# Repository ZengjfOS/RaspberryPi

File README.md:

# README

个人认为，树莓派应该算是目前开源硬件里学习嵌入式Linux系统最好的工具，里面的设计思路和一些工具是很值得借鉴的，这里主要使用Raspberry Pi 4B进行系统架构分析。

## 40 Pin引脚

## Refers

## docs

NO.|文件名称|摘要
:--:|:--|:--
0027| [制作风扇扩展板FanHAT](docs/0027_制作风扇扩展板FanHAT.md) | KiCad制作风扇扩展板FanHaT
0026| [git服务器](docs/0026_git服务器.md) | 搭建git服务器
0025| [硬件PWM控制风扇](docs/0025_硬件PWM控制风扇.md) | PWM控制风扇
0024| [采用V4L2接口获取USB摄像头图片](docs/0024_采用V4L2接口获取USB摄像头图片.md) | C语言获取图片可以更好理解V4L2接口
0023| [关于如何学习](docs/0023_关于如何学习.md) | 记录是最好的反思
0022| [SD卡自动扩容](docs/0022_SD卡自动扩容.md) | 理解SD卡自动扩容工作原理
0021| [wav声音PCM数据分析](docs/0021_wav声音PCM数据分析.md) | 通过wav文件了解PCM数据
0020| [Android_Binder通信](docs/0020_Android_Binder通信.md) | 在树莓派中理解Android Binder通信
0019| [USB_OTG虚拟串口](docs/0019_USB_OTG虚拟串口.md) | USB OTG虚拟串口，可用于学习串口通信
0018| [利用AT24C02_EEPROM理解I2C通信](docs/0018_利用AT24C02_EEPROM理解I2C通信.md) | 利用Overlay加载AT24C02 I2C驱动，通过i2c-tools获取数据
0017| [GPIO中断模式控制网页](docs/0017_GPIO中断模式控制网页.md) | 通过Python3 Flask/websocket作为服务端，使用GPIO控制网页背景
0016| [IoT网页GPIO控制LED](docs/0016_IoT网页GPIO控制LED.md) | 通过Python3 Flask作为HTTP服务端，控制GPIO
0015| [用户空间控制GPIO](docs/0015_用户空间控制GPIO.md) | 通过使用内核GPIO Sysfs Interface在用户空间控制LED
0014| [动态设备树GPIO控制LED](docs/0014_动态设备树GPIO控制LED.md) | 通过使用动态改变设备树，使用内核gpio-poweroff驱动实现LED控制
0013| [开机自动发IP信息邮件](docs/0013_开机自动发IP信息邮件.md) | Python3自动发邮件
0012| [dtparam_dtoverlay_DTS动态设备树](docs/0012_dtparam_dtoverlay_DTS动态设备树.md) | 分析dtparam/dtoverlay本质，为什么能够动态改变设备与驱动的match
0011| [SoC设备树DTS分析](docs/0011_SoC设备树DTS分析.md) | 怎么分析芯片设备树
0010| [Tmux_Vim_Ctags_Cscope代码分析](docs/0010_Tmux_Vim_Ctags_Cscope代码分析.md) | 在Linux命令行如何阅读代码？
0009| [USB摄像头搭建IP网络摄像头](docs/0009_USB摄像头搭建IP网络摄像头.md) | 使用USB Camera搭建IP Camera，理解IP Camera工作原理
0008| [USB摄像头分析udev加载驱动原理](docs/0008_USB摄像头分析udev加载驱动原理.md) | 使用USB Camera分析udev加载驱动原理，理解udev工作原理
0007| [Systemd进程启动](docs/0007_Systemd进程启动.md) | 分析Linux系统进程何启动起来
0006| [搭建samba服务端](docs/0006_搭建samba服务端.md) | 像访问普通文件夹一样访问树莓派文件系统
0005| [内核编译](docs/0005_内核编译.md) | 编译Linux内核，以备后续修改及分析驱动
0004| [Debug串口](docs/0004_Debug串口.md) | 看内核启动log信息，当机器无法启动可以判定问题
0003| [开源软件镜像站加速](docs/0003_开源软件镜像站加速.md) | 时间很宝贵，只介绍apt、pip镜像站，其他可自行扩展
0002| [USB_OTG虚拟网卡](docs/0002_USB_OTG虚拟网卡.md) | 在有些场合，没有Wifi想登陆树莓派，使用USB虚拟网卡SSH登陆
0001| [无屏如何使用树莓派](docs/0001_无屏如何使用树莓派.md) | 一个屏比一个树莓派还贵，不大可能为了玩个树莓派还单独买个屏，并不是每个人都有屏的需求

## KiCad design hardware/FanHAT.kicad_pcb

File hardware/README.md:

# README

风扇HAT板KiCad工程

## 打样

* [FanHAT.zip](FanHAT.zip)

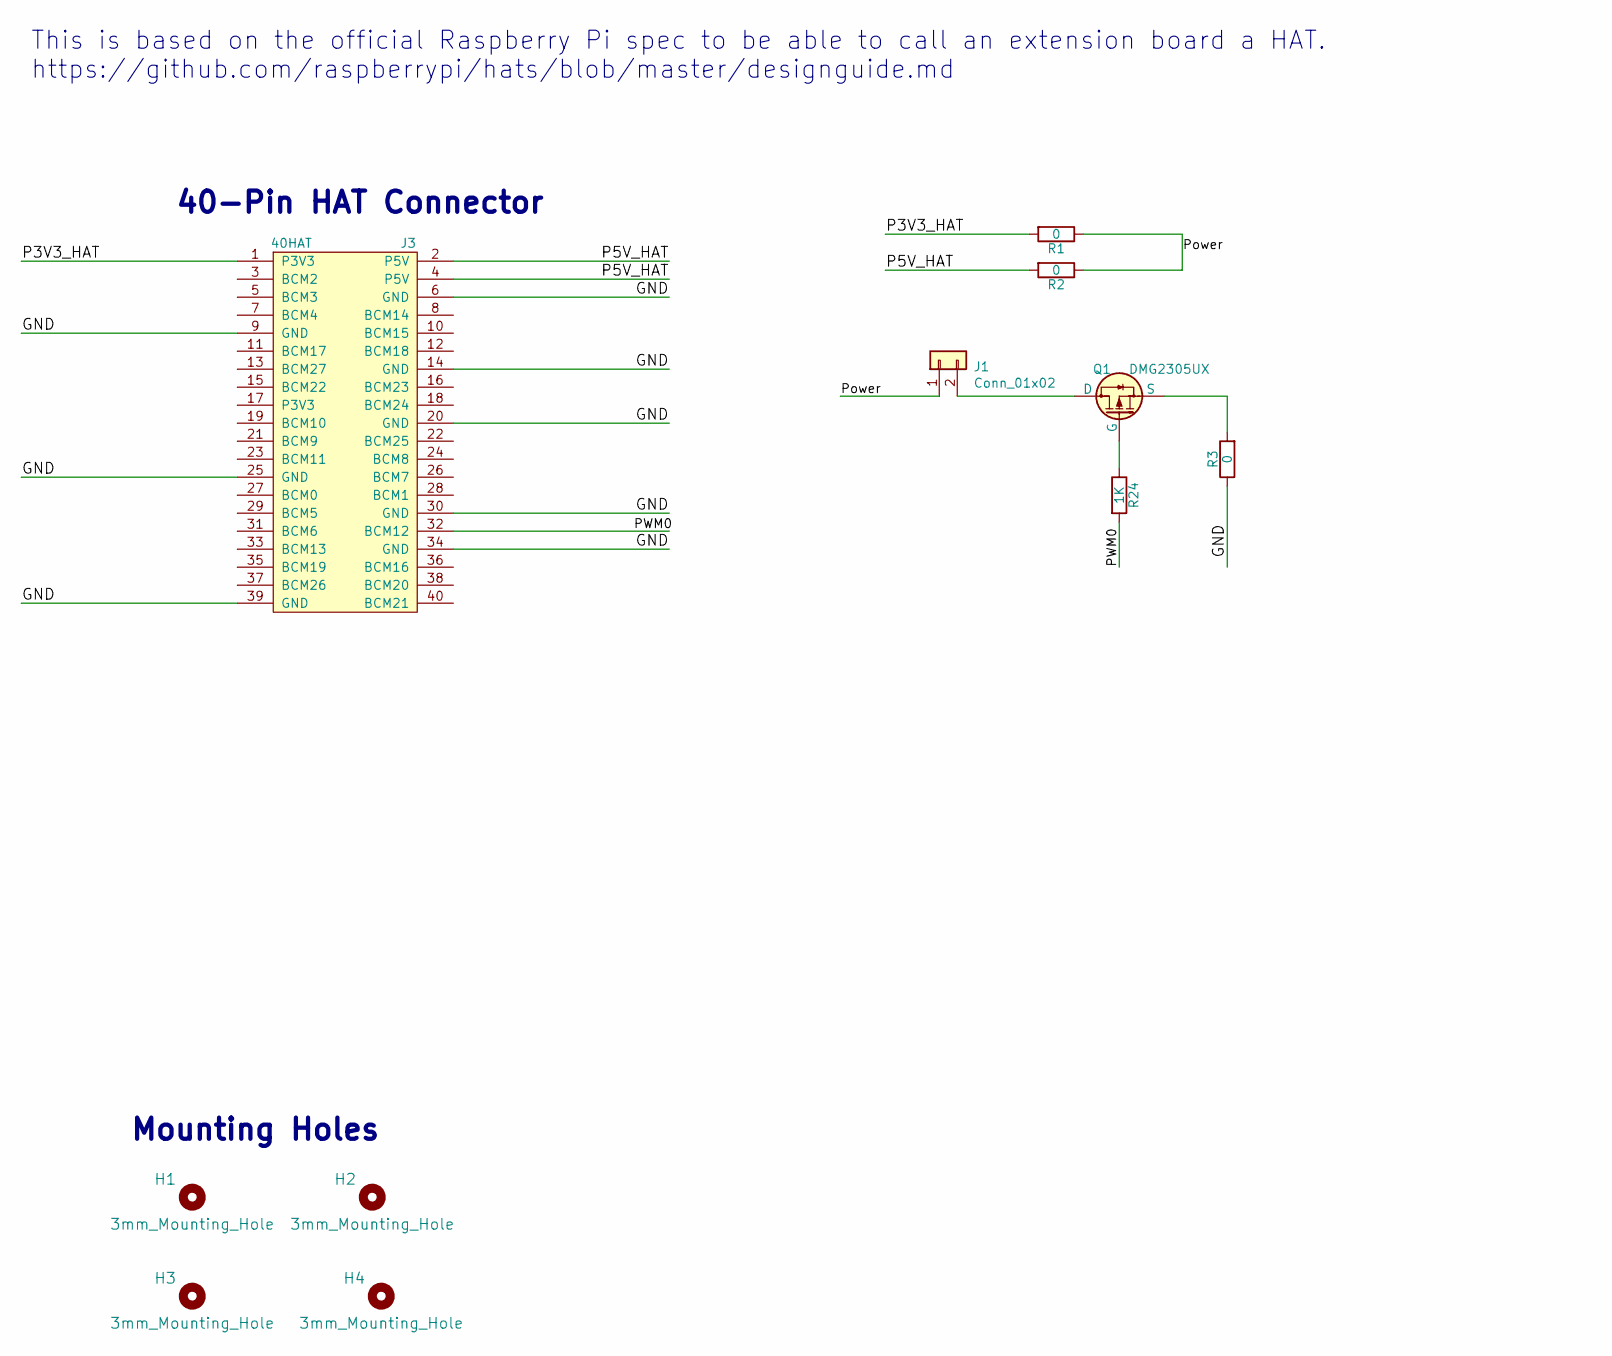
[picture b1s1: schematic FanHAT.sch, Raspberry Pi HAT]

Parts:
H1, H2, H3, H4: 3mm_Mounting_Hole; NPTH_3mm_ID
J1: Conn_01x02; PinHeader_1x02_P2.54mm_Vertical
J3: 40HAT; PinSocket_2x20_P2.54mm_Vertical
Q1: DMG2305UX; SOT-23
R1, R2, R3: 0; R_0603_1608Metric
R24: 1K; R_0603_1608Metric

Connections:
/GND: J3.6 (GND), J3.9 (GND), J3.14 (GND), J3.20 (GND), J3.25 (GND), J3.30 (GND), J3.34 (GND), J3.39 (GND), R3.1
/P3V3_HAT: J3.1 (P3V3), R1.2
/P5V_HAT: J3.2 (P5V), J3.4 (P5V), R2.2
/PWM0: J3.32 (BCM12), R24.2
/Power: J1.1, R1.1, R2.1
unnamed: J1.2, Q1.3 (D)
unnamed: Q1.1 (G), R24.1
unnamed: Q1.2 (S), R3.2

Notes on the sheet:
Mounting Holes
40-Pin HAT Connector
This is based on the official Raspberry Pi spec to be able to call an extension board a HAT. https://github.com/raspberrypi/hats/blob/master/designguide.md

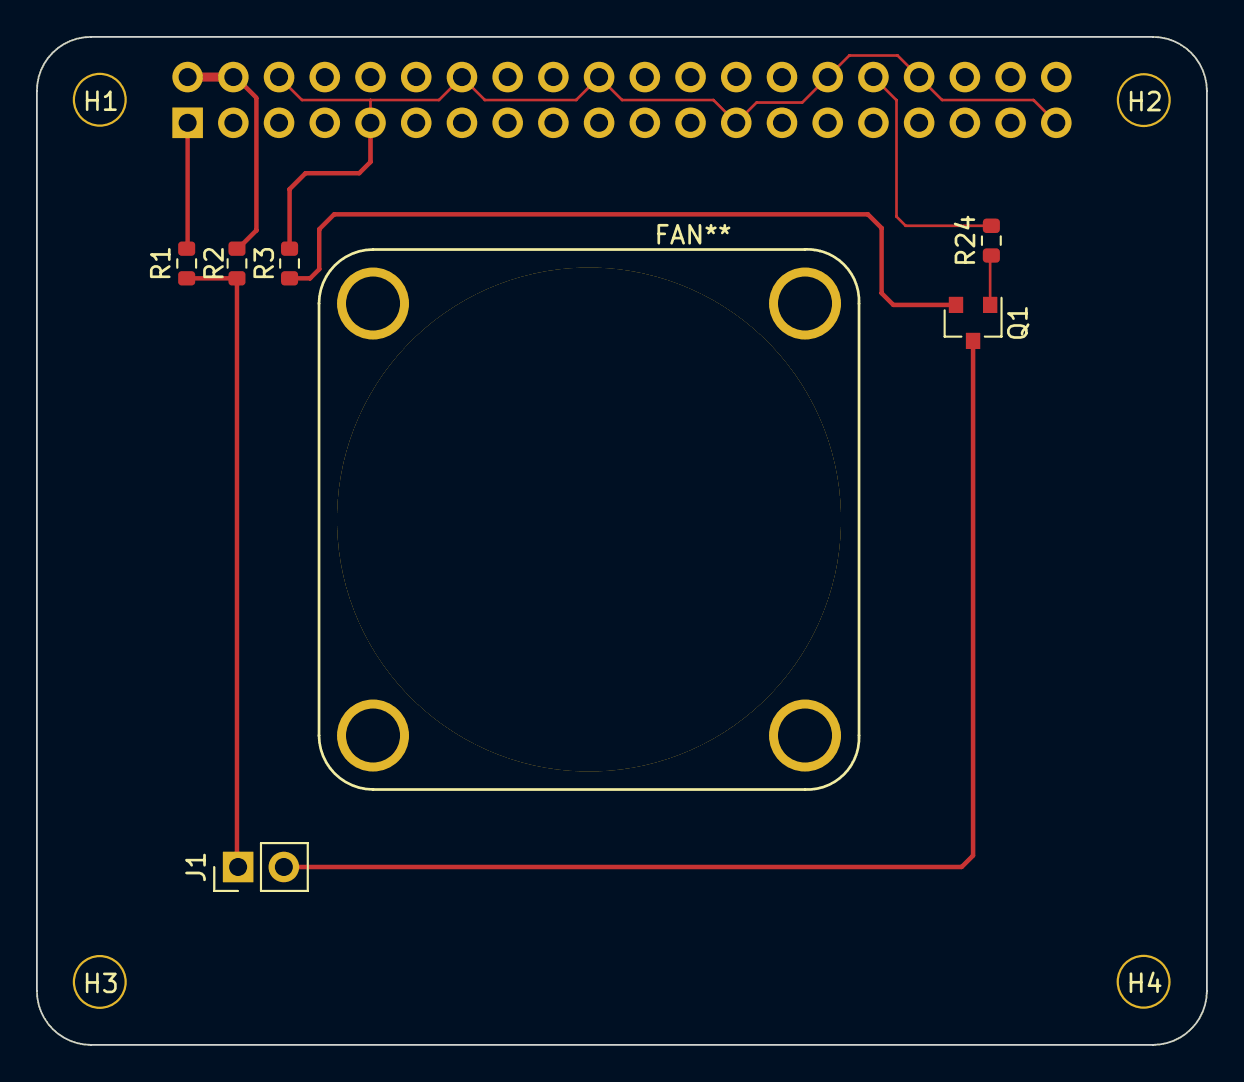
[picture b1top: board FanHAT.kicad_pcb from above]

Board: 2 copper layers, 65.0 x 56.0 mm, 12 parts (1 on the bottom side), 8 nets.

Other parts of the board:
FAN**: FAN_3x3mm

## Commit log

2019-08-28 init branch
2019-08-29 support irq type
2020-04-08 init
2020-11-24 simulation
2020-12-01 client service
2020-12-02 diff for android
2020-12-12 for test concurrent processing
2021-01-31 usb/mirror
2021-02-10 debug port
2021-02-10 compile kernel
2021-02-10 samba
2021-02-12 initt
2021-02-13 udev
2021-02-16 usb camera
2021-02-18 fix make clean error
2021-02-19 android q
2021-02-21 gpio power off
2021-02-21 export gpio
2021-02-21 led contorl
2021-02-21 iot led
2021-02-27 button
2021-02-27 button for web
2021-02-27 i2c eeprom
2021-02-27 otg uart
2021-03-05 binder
2021-03-07 docs/0021_wav声音PCM数据分析.md
2021-03-14 SD expand
2021-03-21 learn
2021-03-27 v4l2 interface
2021-03-27 fan pwm
2021-04-03 hardware
2021-04-10 modify for enable
2021-04-18 fanhat
